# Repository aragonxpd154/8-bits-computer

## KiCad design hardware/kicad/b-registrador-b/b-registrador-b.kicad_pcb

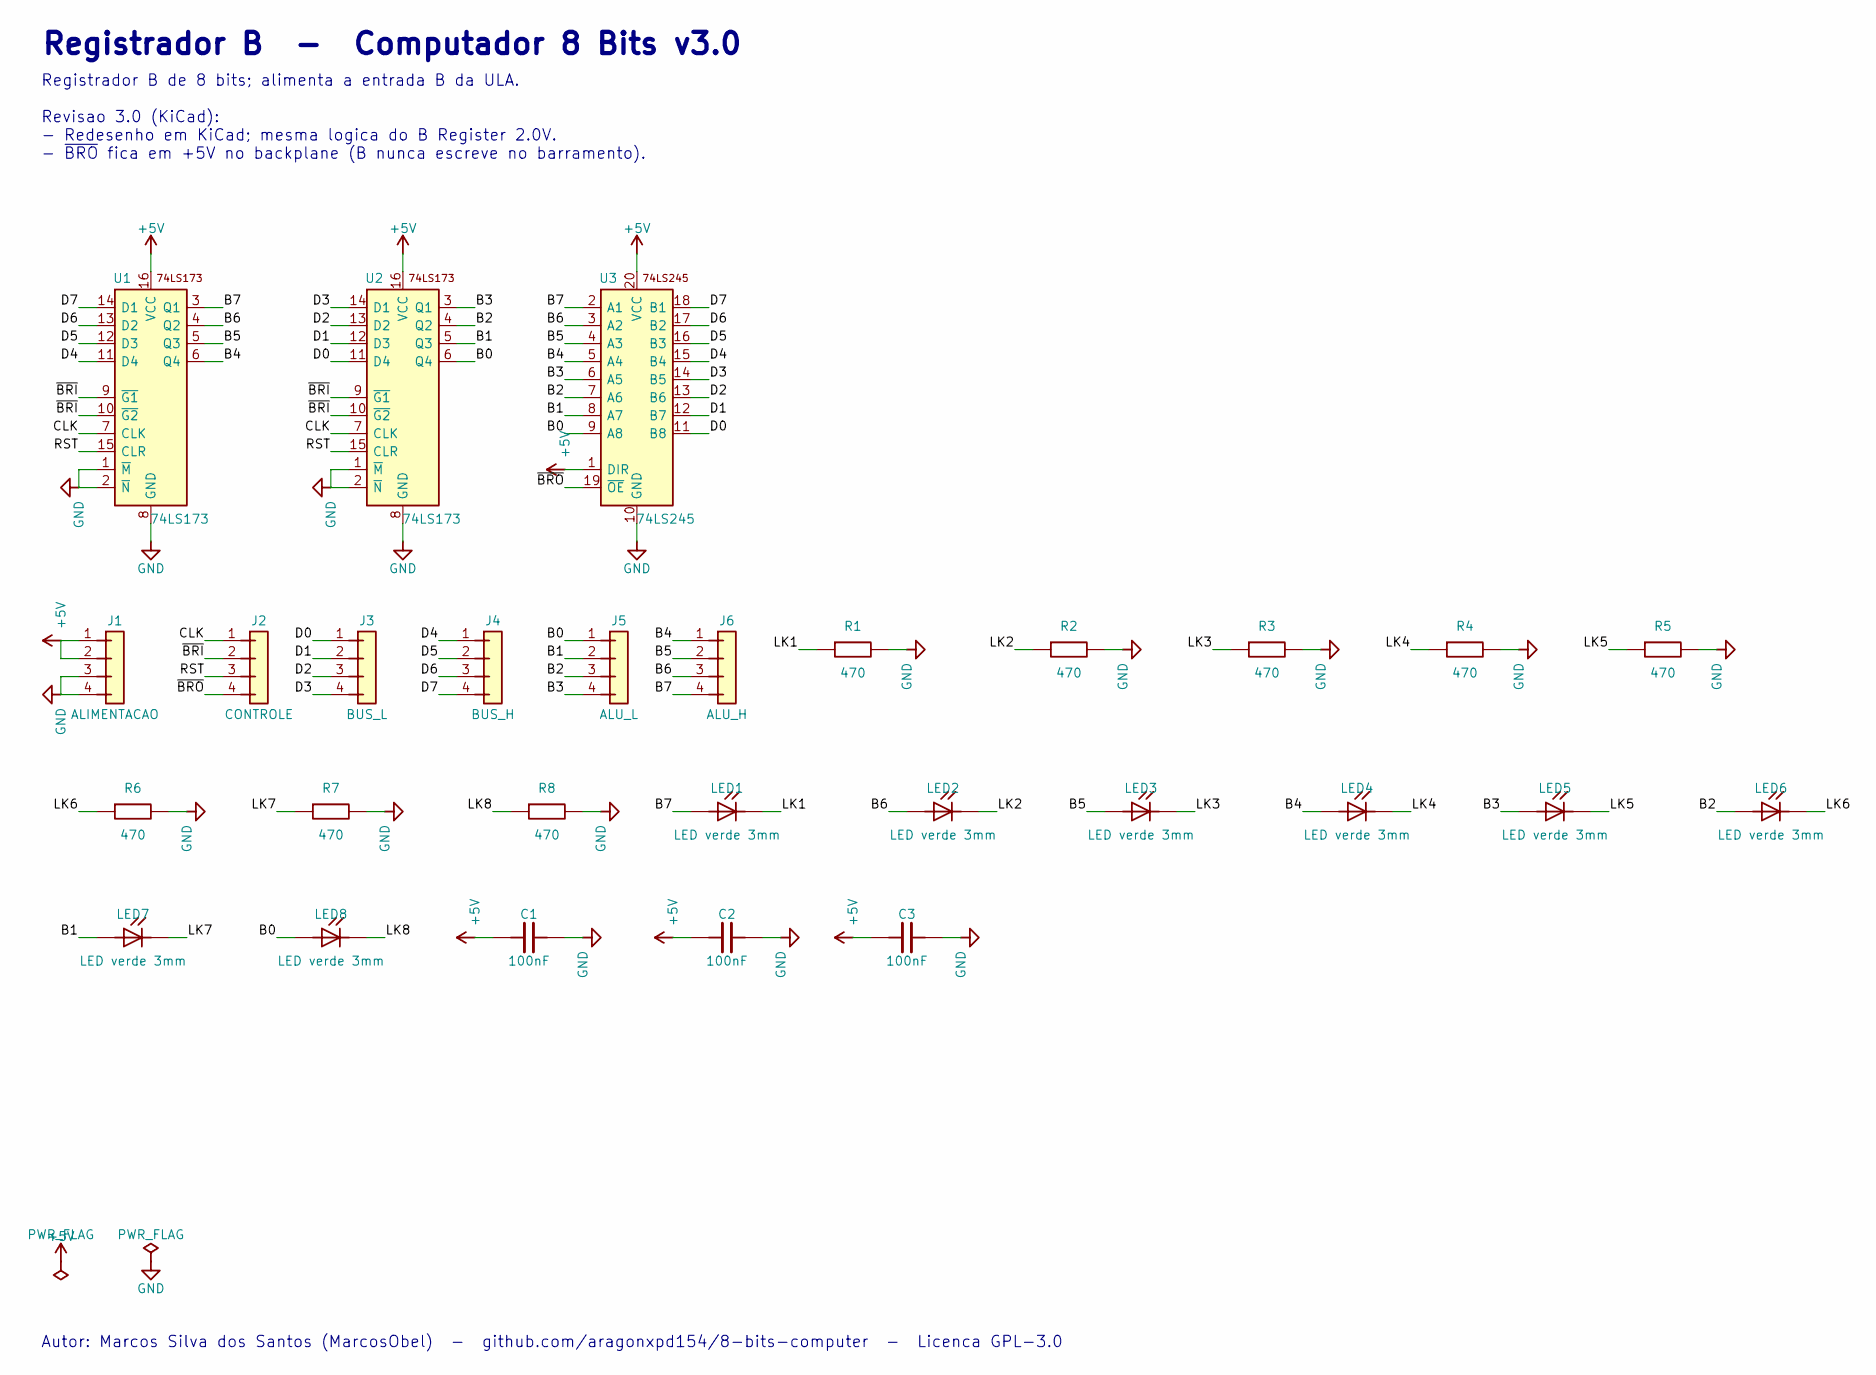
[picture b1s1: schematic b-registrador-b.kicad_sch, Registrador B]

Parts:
C1, C2, C3: 100nF; C_Disc_D5.0mm_W2.5mm_P5.00mm
J1: ALIMENTACAO; PinHeader_1x04_P2.54mm_Vertical
J2: CONTROLE; PinHeader_1x04_P2.54mm_Vertical
J3: BUS_L; PinHeader_1x04_P2.54mm_Vertical
J4: BUS_H; PinHeader_1x04_P2.54mm_Vertical
J5: ALU_L; PinHeader_1x04_P2.54mm_Vertical
J6: ALU_H; PinHeader_1x04_P2.54mm_Vertical
LED1, LED2, LED3, LED4, LED5, LED6, LED7, LED8: LED verde 3mm; LED_D3.0mm
R1, R2, R3, R4, R5, R6, R7, R8: 470; R_Axial_DIN0207_L6.3mm_D2.5mm_P10.16mm_Horizontal
U1, U2: 74LS173; DIP-16_W7.62mm_LongPads
U3: 74LS245; DIP-20_W7.62mm_LongPads

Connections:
+5V: C1.1, C2.1, C3.1, J1.1, J1.2, U1.16 (VCC), U2.16 (VCC), U3.1 (DIR), U3.20 (VCC)
B0: J5.1, LED8.2 (A), U2.6 (Q4), U3.9 (A8)
B1: J5.2, LED7.2 (A), U2.5 (Q3), U3.8 (A7)
B2: J5.3, LED6.2 (A), U2.4 (Q2), U3.7 (A6)
B3: J5.4, LED5.2 (A), U2.3 (Q1), U3.6 (A5)
B4: J6.1, LED4.2 (A), U1.6 (Q4), U3.5 (A4)
B5: J6.2, LED3.2 (A), U1.5 (Q3), U3.4 (A3)
B6: J6.3, LED2.2 (A), U1.4 (Q2), U3.3 (A2)
B7: J6.4, LED1.2 (A), U1.3 (Q1), U3.2 (A1)
CLK: J2.1, U1.7 (CLK), U2.7 (CLK)
D0: J3.1, U2.11 (D4), U3.11 (B8)
D1: J3.2, U2.12 (D3), U3.12 (B7)
D2: J3.3, U2.13 (D2), U3.13 (B6)
D3: J3.4, U2.14 (D1), U3.14 (B5)
D4: J4.1, U1.11 (D4), U3.15 (B4)
D5: J4.2, U1.12 (D3), U3.16 (B3)
D6: J4.3, U1.13 (D2), U3.17 (B2)
D7: J4.4, U1.14 (D1), U3.18 (B1)
GND: C1.2, C2.2, C3.2, J1.3, J1.4, R1.2, R2.2, R3.2, R4.2, R5.2, R6.2, R7.2, R8.2, U1.1 (~M), U1.2 (~N), U1.8 (GND), U2.1 (~M), U2.2 (~N), U2.8 (GND), U3.10 (GND)
LK1: LED1.1 (K), R1.1
LK2: LED2.1 (K), R2.1
LK3: LED3.1 (K), R3.1
LK4: LED4.1 (K), R4.1
LK5: LED5.1 (K), R5.1
LK6: LED6.1 (K), R6.1
LK7: LED7.1 (K), R7.1
LK8: LED8.1 (K), R8.1
RST: J2.3, U1.15 (CLR), U2.15 (CLR)
~BRI: J2.2, U1.9 (~G1), U1.10 (~G2), U2.9 (~G1), U2.10 (~G2)
~BRO: J2.4, U3.19 (~OE)

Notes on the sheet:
Registrador B - Computador 8 Bits v3.0
Registrador B de 8 bits; alimenta a entrada B da ULA. Revisao 3.0 (KiCad): - Redesenho em KiCad; mesma logica do B Register 2.0V. - ~{BRO} fica em +5V no backplane (B nunca escreve no barramento).
Autor: Marcos Silva dos Santos (MarcosObel) - github.com/aragonxpd154/8-bits-computer - Licenca GPL-3.0

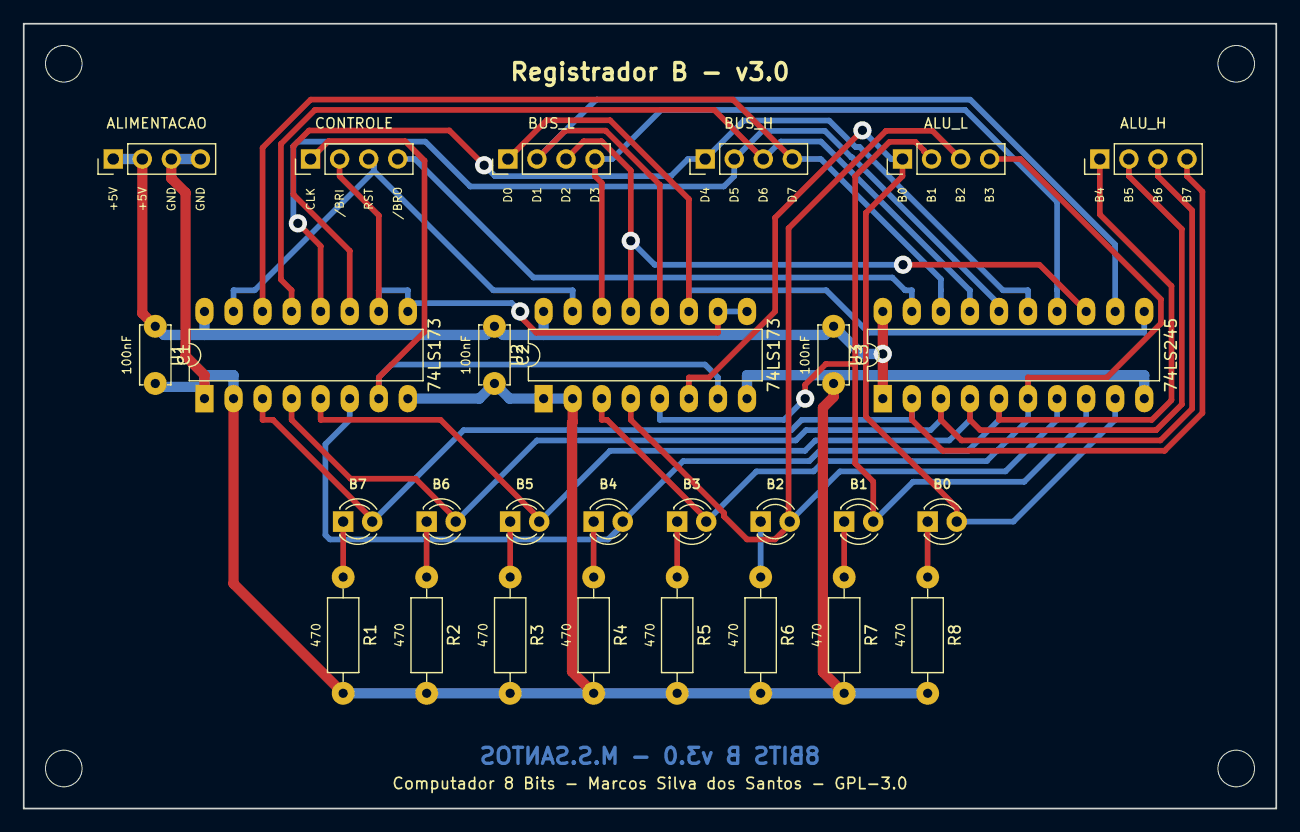
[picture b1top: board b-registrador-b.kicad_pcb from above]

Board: 2 copper layers, 109.5 x 68.6 mm, 32 parts (0 on the bottom side), 30 nets.

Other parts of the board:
H1, H2, H3, H4: MountingHole_3.2mm_M3

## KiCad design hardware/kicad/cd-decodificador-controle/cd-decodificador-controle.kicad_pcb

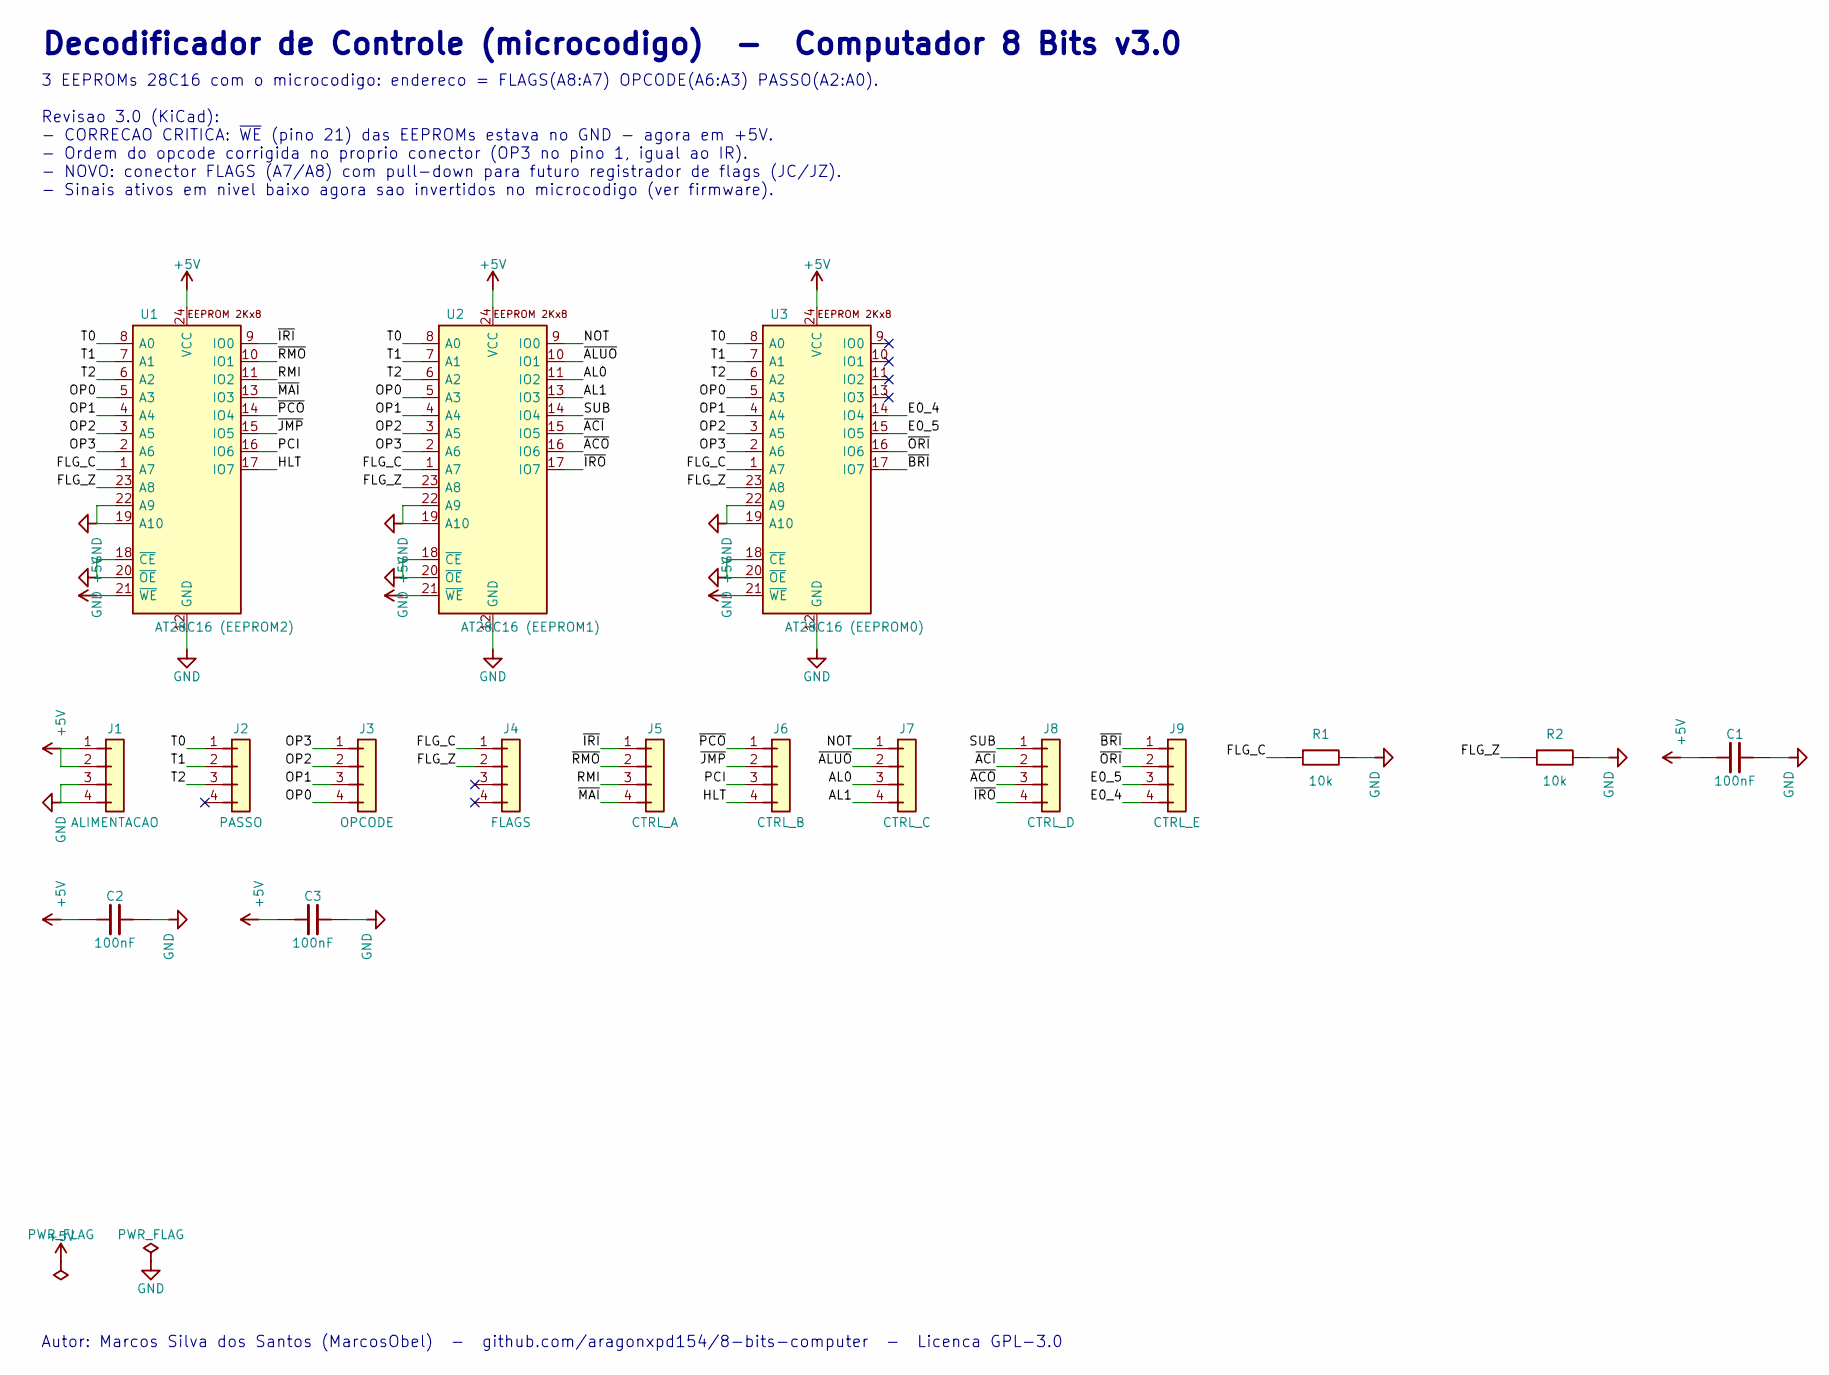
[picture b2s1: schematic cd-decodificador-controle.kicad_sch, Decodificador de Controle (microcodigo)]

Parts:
C1, C2, C3: 100nF; C_Disc_D5.0mm_W2.5mm_P5.00mm
J1: ALIMENTACAO; PinHeader_1x04_P2.54mm_Vertical
J2: PASSO; PinHeader_1x04_P2.54mm_Vertical
J3: OPCODE; PinHeader_1x04_P2.54mm_Vertical
J4: FLAGS; PinHeader_1x04_P2.54mm_Vertical
J5: CTRL_A; PinHeader_1x04_P2.54mm_Vertical
J6: CTRL_B; PinHeader_1x04_P2.54mm_Vertical
J7: CTRL_C; PinHeader_1x04_P2.54mm_Vertical
J8: CTRL_D; PinHeader_1x04_P2.54mm_Vertical
J9: CTRL_E; PinHeader_1x04_P2.54mm_Vertical
R1, R2: 10k; R_Axial_DIN0207_L6.3mm_D2.5mm_P10.16mm_Horizontal
U1: AT28C16 (EEPROM2); DIP-24_W15.24mm_LongPads
U2: AT28C16 (EEPROM1); DIP-24_W15.24mm_LongPads
U3: AT28C16 (EEPROM0); DIP-24_W15.24mm_LongPads

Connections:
+5V: C1.1, C2.1, C3.1, J1.1, J1.2, U1.21 (~WE), U1.24 (VCC), U2.21 (~WE), U2.24 (VCC), U3.21 (~WE), U3.24 (VCC)
AL0: J7.3, U2.11 (IO2)
AL1: J7.4, U2.13 (IO3)
E0_4: J9.4, U3.14 (IO4)
E0_5: J9.3, U3.15 (IO5)
FLG_C: J4.1, R1.1, U1.1 (A7), U2.1 (A7), U3.1 (A7)
FLG_Z: J4.2, R2.1, U1.23 (A8), U2.23 (A8), U3.23 (A8)
GND: C1.2, C2.2, C3.2, J1.3, J1.4, R1.2, R2.2, U1.12 (GND), U1.18 (~CE), U1.19 (A10), U1.20 (~OE), U1.22 (A9), U2.12 (GND), U2.18 (~CE), U2.19 (A10), U2.20 (~OE), U2.22 (A9), U3.12 (GND), U3.18 (~CE), U3.19 (A10), U3.20 (~OE), U3.22 (A9)
HLT: J6.4, U1.17 (IO7)
NOT: J7.1, U2.9 (IO0)
OP0: J3.4, U1.5 (A3), U2.5 (A3), U3.5 (A3)
OP1: J3.3, U1.4 (A4), U2.4 (A4), U3.4 (A4)
OP2: J3.2, U1.3 (A5), U2.3 (A5), U3.3 (A5)
OP3: J3.1, U1.2 (A6), U2.2 (A6), U3.2 (A6)
PCI: J6.3, U1.16 (IO6)
RMI: J5.3, U1.11 (IO2)
SUB: J8.1, U2.14 (IO4)
T0: J2.1, U1.8 (A0), U2.8 (A0), U3.8 (A0)
T1: J2.2, U1.7 (A1), U2.7 (A1), U3.7 (A1)
T2: J2.3, U1.6 (A2), U2.6 (A2), U3.6 (A2)
~ACI: J8.2, U2.15 (IO5)
~ACO: J8.3, U2.16 (IO6)
~ALUO: J7.2, U2.10 (IO1)
~BRI: J9.1, U3.17 (IO7)
~IRI: J5.1, U1.9 (IO0)
~IRO: J8.4, U2.17 (IO7)
~JMP: J6.2, U1.15 (IO5)
~MAI: J5.4, U1.13 (IO3)
~ORI: J9.2, U3.16 (IO6)
~PCO: J6.1, U1.14 (IO4)
~RMO: J5.2, U1.10 (IO1)

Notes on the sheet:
Decodificador de Controle (microcodigo) - Computador 8 Bits v3.0
3 EEPROMs 28C16 com o microcodigo: endereco = FLAGS(A8:A7) OPCODE(A6:A3) PASSO(A2:A0). Revisao 3.0 (KiCad): - CORRECAO CRITICA: ~{WE} (pino 21) das EEPROMs estava no GND - agora em +5V. - Ordem do opcode corrigida no proprio conector (OP3 no pino 1, igual ao IR). - NOVO: conector FLAGS (A7/A8) com 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
Autor: Marcos Silva dos Santos (MarcosObel) - github.com/aragonxpd154/8-bits-computer - Licenca GPL-3.0

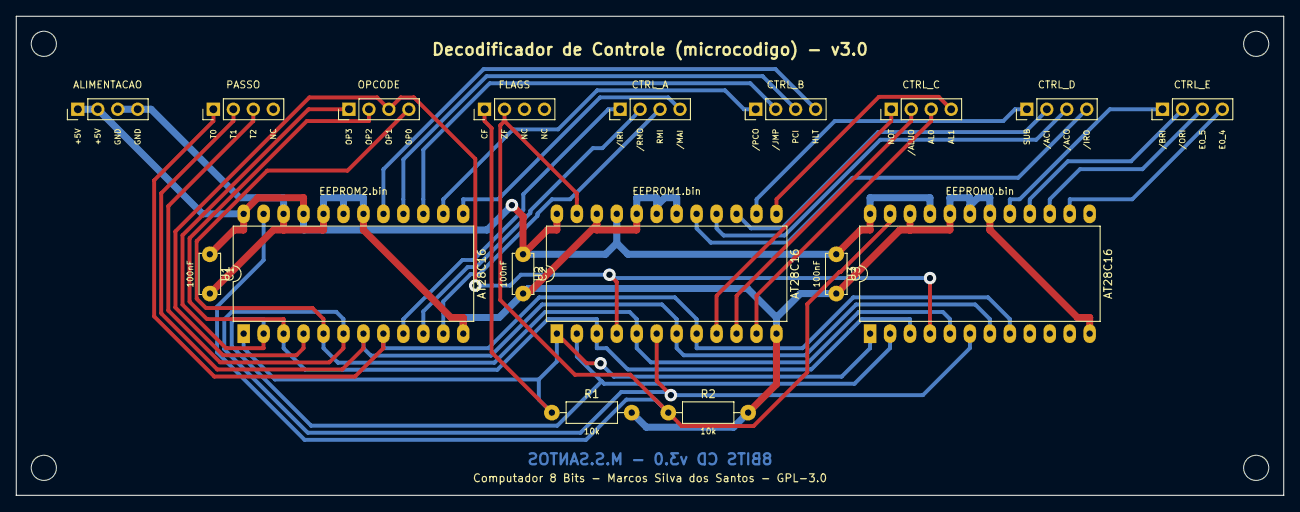
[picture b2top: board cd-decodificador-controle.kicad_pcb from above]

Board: 2 copper layers, 161.2 x 61.0 mm, 21 parts (0 on the bottom side), 31 nets.

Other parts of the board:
H1, H2, H3, H4: MountingHole_3.2mm_M3

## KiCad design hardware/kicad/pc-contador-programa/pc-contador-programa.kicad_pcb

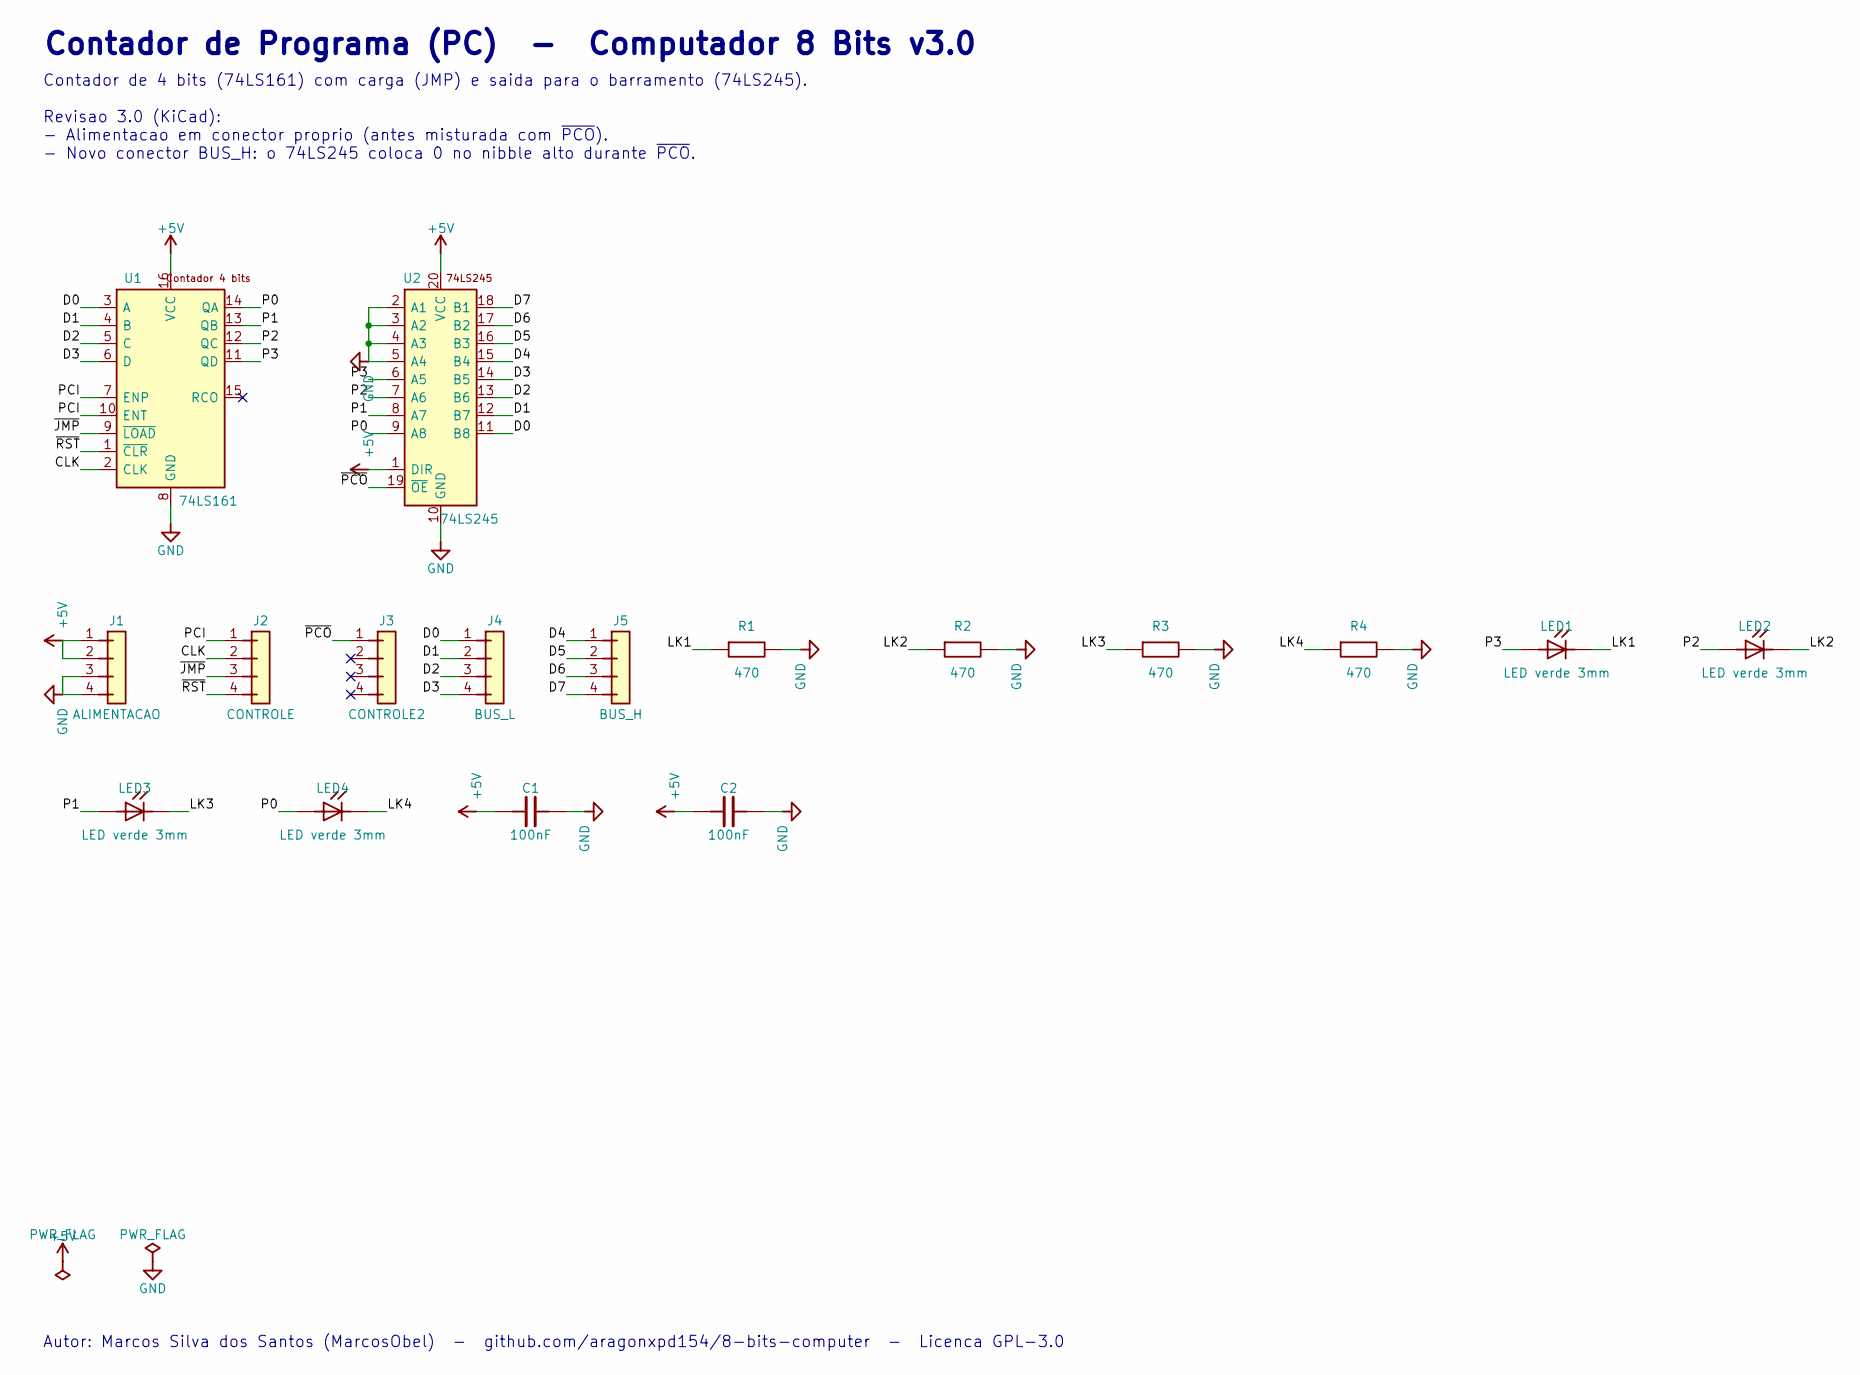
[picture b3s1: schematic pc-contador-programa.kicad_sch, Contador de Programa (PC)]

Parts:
C1, C2: 100nF; C_Disc_D5.0mm_W2.5mm_P5.00mm
J1: ALIMENTACAO; PinHeader_1x04_P2.54mm_Vertical
J2: CONTROLE; PinHeader_1x04_P2.54mm_Vertical
J3: CONTROLE2; PinHeader_1x04_P2.54mm_Vertical
J4: BUS_L; PinHeader_1x04_P2.54mm_Vertical
J5: BUS_H; PinHeader_1x04_P2.54mm_Vertical
LED1, LED2, LED3, LED4: LED verde 3mm; LED_D3.0mm
R1, R2, R3, R4: 470; R_Axial_DIN0207_L6.3mm_D2.5mm_P10.16mm_Horizontal
U1: 74LS161; DIP-16_W7.62mm_LongPads
U2: 74LS245; DIP-20_W7.62mm_LongPads

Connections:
+5V: C1.1, C2.1, J1.1, J1.2, U1.16 (VCC), U2.1 (DIR), U2.20 (VCC)
CLK: J2.2, U1.2 (CLK)
D0: J4.1, U1.3 (A), U2.11 (B8)
D1: J4.2, U1.4 (B), U2.12 (B7)
D2: J4.3, U1.5 (C), U2.13 (B6)
D3: J4.4, U1.6 (D), U2.14 (B5)
D4: J5.1, U2.15 (B4)
D5: J5.2, U2.16 (B3)
D6: J5.3, U2.17 (B2)
D7: J5.4, U2.18 (B1)
GND: C1.2, C2.2, J1.3, J1.4, R1.2, R2.2, R3.2, R4.2, U1.8 (GND), U2.2 (A1), U2.3 (A2), U2.4 (A3), U2.5 (A4), U2.10 (GND)
LK1: LED1.1 (K), R1.1
LK2: LED2.1 (K), R2.1
LK3: LED3.1 (K), R3.1
LK4: LED4.1 (K), R4.1
P0: LED4.2 (A), U1.14 (QA), U2.9 (A8)
P1: LED3.2 (A), U1.13 (QB), U2.8 (A7)
P2: LED2.2 (A), U1.12 (QC), U2.7 (A6)
P3: LED1.2 (A), U1.11 (QD), U2.6 (A5)
PCI: J2.1, U1.7 (ENP), U1.10 (ENT)
~JMP: J2.3, U1.9 (~LOAD)
~PCO: J3.1, U2.19 (~OE)
~RST: J2.4, U1.1 (~CLR)

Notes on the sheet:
Contador de Programa (PC) - Computador 8 Bits v3.0
Contador de 4 bits (74LS161) com carga (JMP) e saida para o barramento (74LS245). Revisao 3.0 (KiCad): - Alimentacao em conector proprio (antes misturada com ~{PCO}). - Novo conector BUS_H: o 74LS245 coloca 0 no nibble alto durante ~{PCO}.
Autor: Marcos Silva dos Santos (MarcosObel) - github.com/aragonxpd154/8-bits-computer - Licenca GPL-3.0

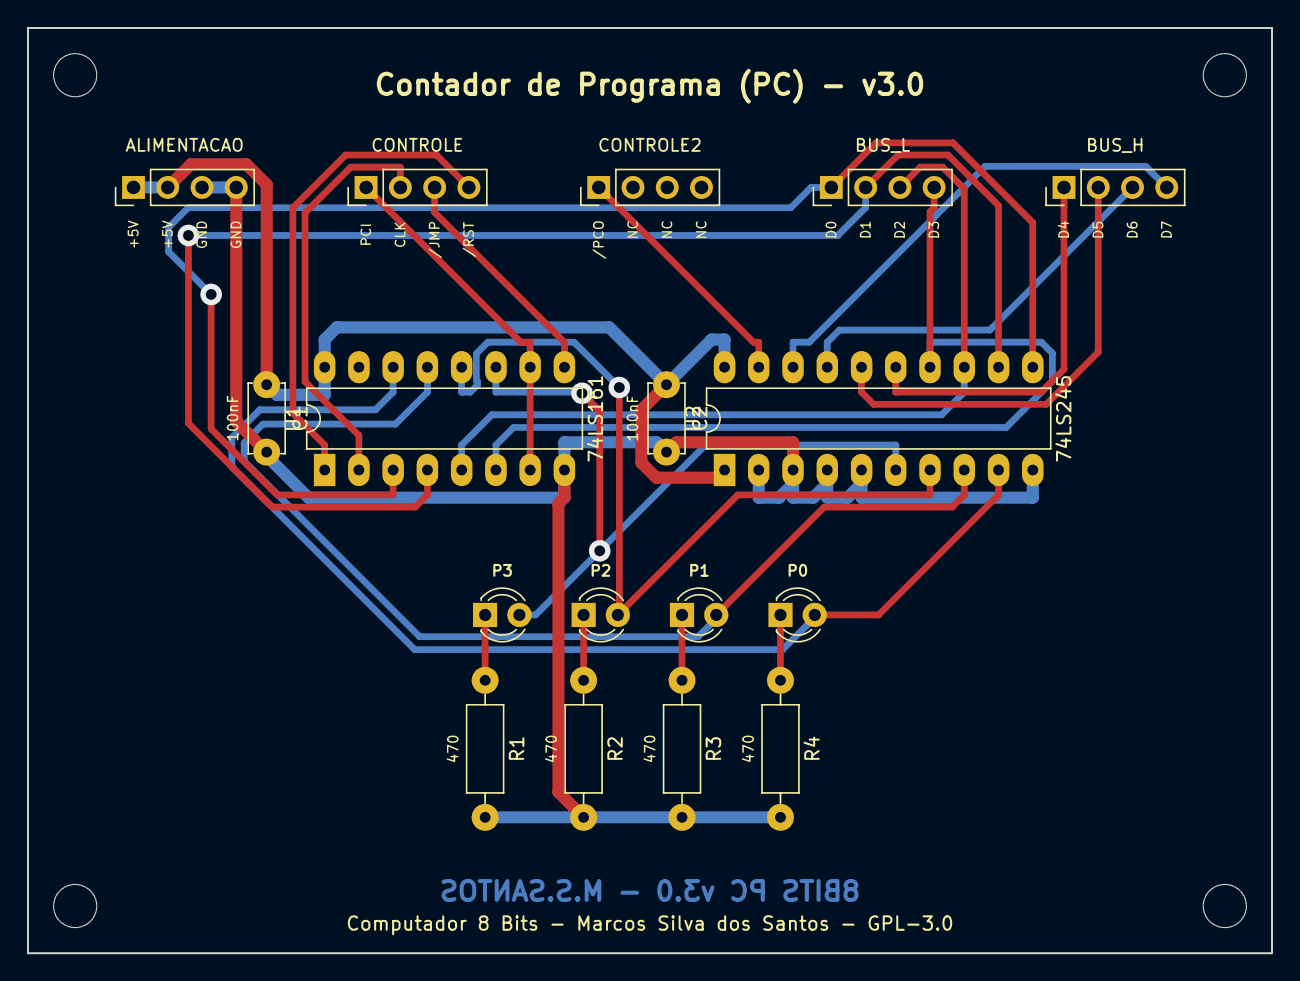
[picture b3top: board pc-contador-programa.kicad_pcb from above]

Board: 2 copper layers, 92.2 x 68.6 mm, 21 parts (0 on the bottom side), 23 nets.

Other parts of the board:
H1, H2, H3, H4: MountingHole_3.2mm_M3

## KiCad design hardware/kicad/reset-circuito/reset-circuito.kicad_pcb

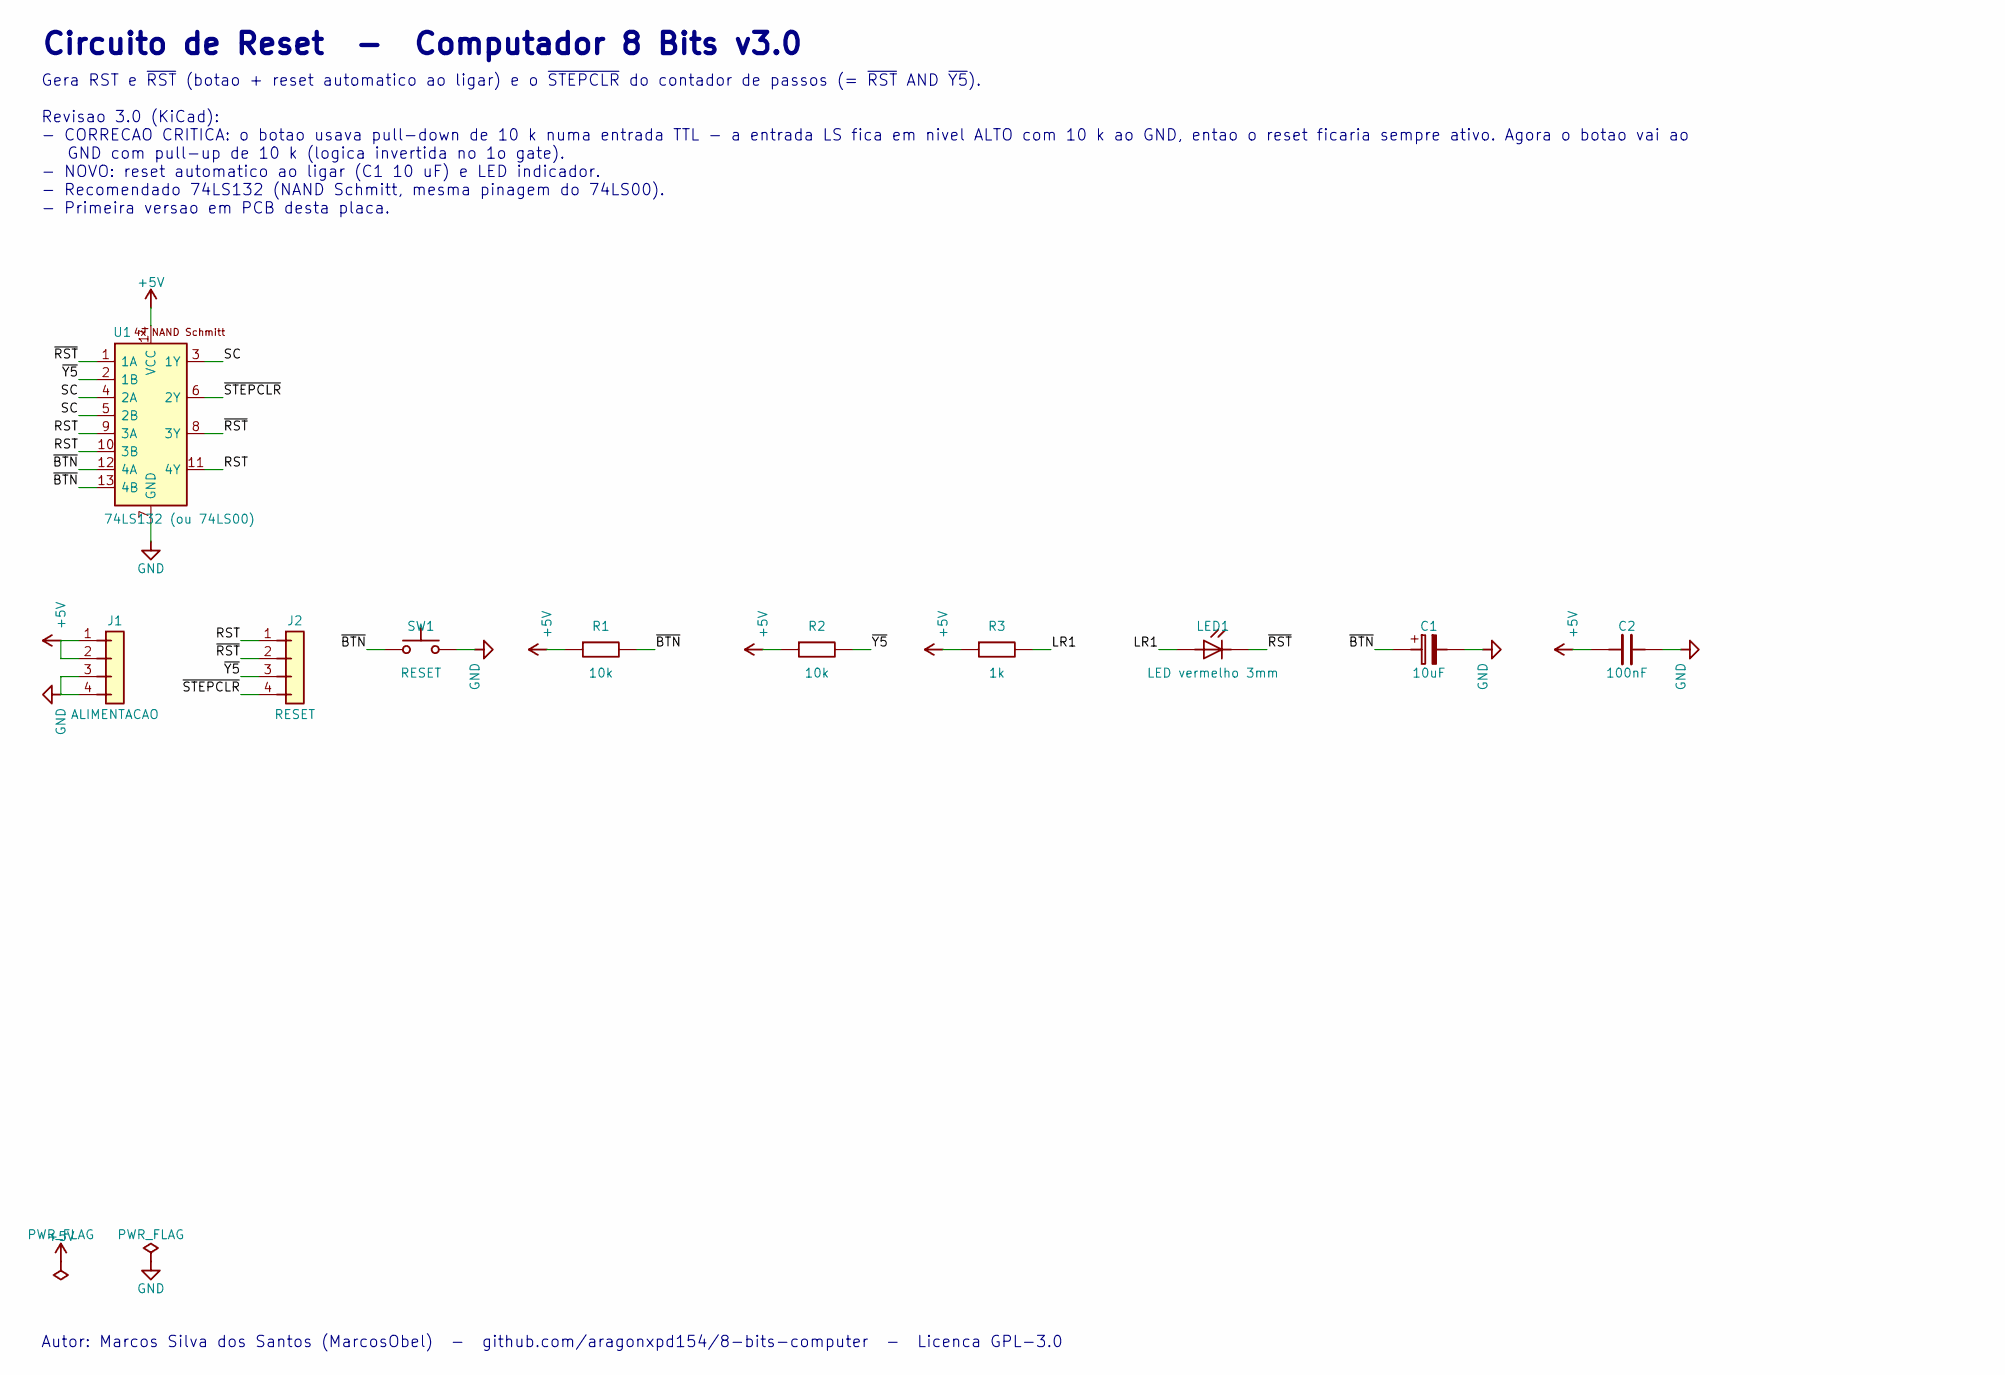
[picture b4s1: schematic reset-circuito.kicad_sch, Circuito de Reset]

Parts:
C1: 10uF; CP_Radial_D5.0mm_P2.00mm
C2: 100nF; C_Disc_D5.0mm_W2.5mm_P5.00mm
J1: ALIMENTACAO; PinHeader_1x04_P2.54mm_Vertical
J2: RESET; PinHeader_1x04_P2.54mm_Vertical
LED1: LED vermelho 3mm; LED_D3.0mm
R1, R2: 10k; R_Axial_DIN0207_L6.3mm_D2.5mm_P10.16mm_Horizontal
R3: 1k; R_Axial_DIN0207_L6.3mm_D2.5mm_P10.16mm_Horizontal
SW1: RESET; SW_PUSH_6mm
U1: 74LS132 (ou 74LS00); DIP-14_W7.62mm_LongPads

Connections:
+5V: C2.1, J1.1, J1.2, R1.1, R2.1, R3.1, U1.14 (VCC)
GND: C1.2, C2.2, J1.3, J1.4, SW1.2, U1.7 (GND)
LR1: LED1.2 (A), R3.2
RST: J2.1, U1.9 (3A), U1.10 (3B), U1.11 (4Y)
SC: U1.3 (1Y), U1.4 (2A), U1.5 (2B)
~BTN: C1.1, R1.2, SW1.1, U1.12 (4A), U1.13 (4B)
~RST: J2.2, LED1.1 (K), U1.1 (1A), U1.8 (3Y)
~STEPCLR: J2.4, U1.6 (2Y)
~Y5: J2.3, R2.2, U1.2 (1B)

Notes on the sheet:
Circuito de Reset - Computador 8 Bits v3.0
Gera RST e ~{RST} (botao + reset automatico ao ligar) e o ~{STEPCLR} do contador de passos (= ~{RST} AND ~{Y5}). Revisao 3.0 (KiCad): - CORRECAO CRITICA: o botao usava pull-down de 10 k numa entrada TTL - a entrada LS fica em nivel ALTO com 10 k ao GND, entao o reset ficaria sempre ativo. Agora o b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
Autor: Marcos Silva dos Santos (MarcosObel) - github.com/aragonxpd154/8-bits-computer - Licenca GPL-3.0

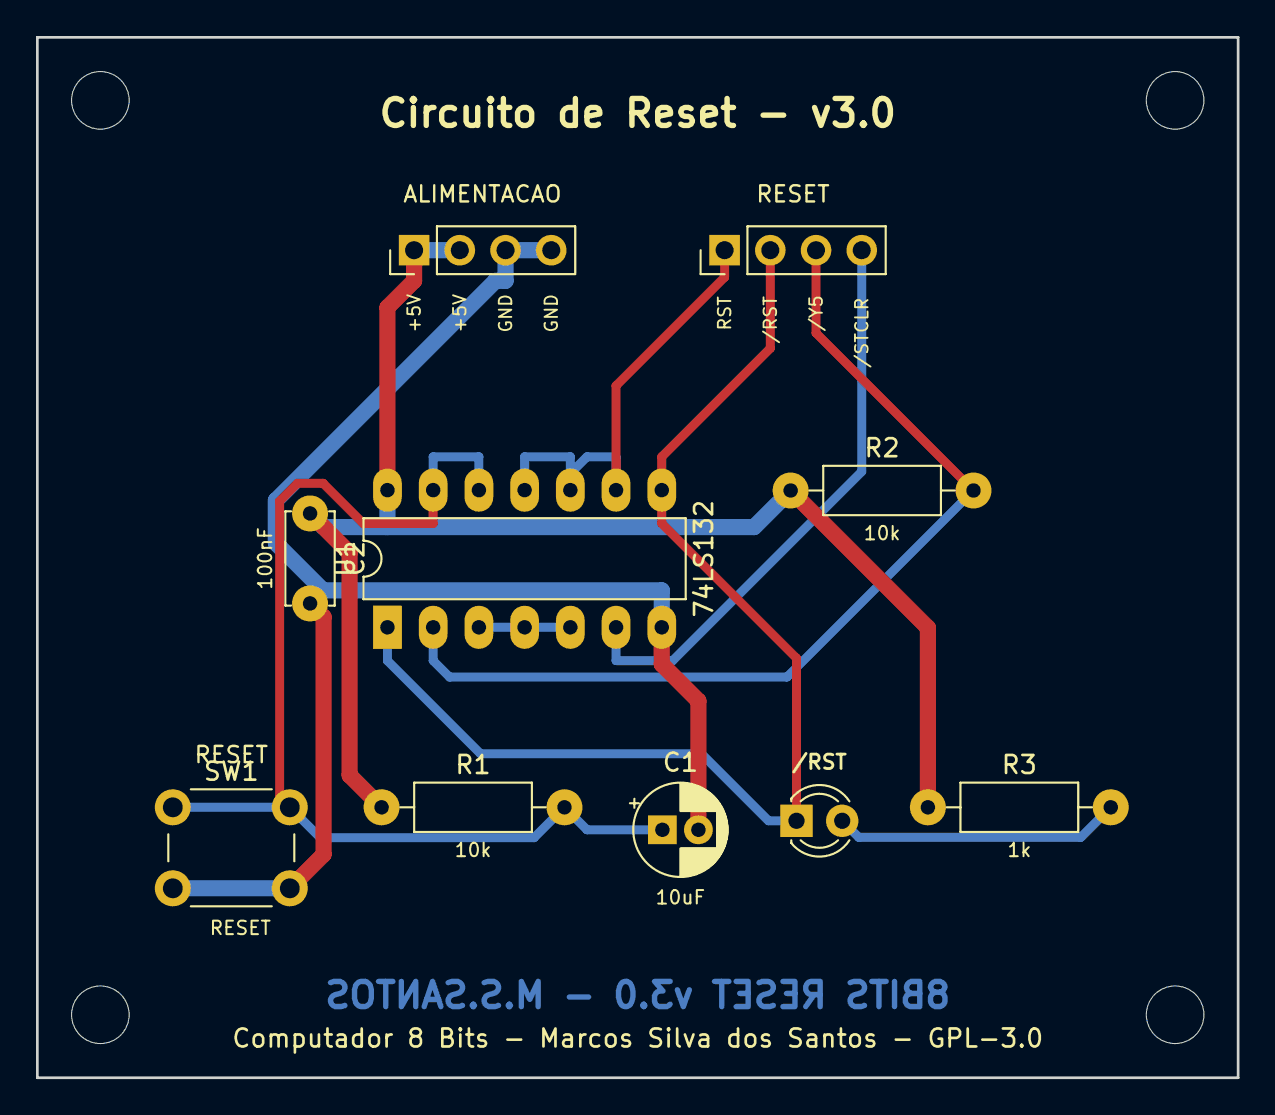
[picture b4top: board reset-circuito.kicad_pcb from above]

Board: 2 copper layers, 66.7 x 57.8 mm, 14 parts (0 on the bottom side), 9 nets.

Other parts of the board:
H1, H2, H3, H4: MountingHole_3.2mm_M3

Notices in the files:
hardware/kicad/b-registrador-b/b-registrador-b.kicad_pcb:
github.com/aragonxpd154/8-bits-computer - GPL-3.0
Computador 8 Bits - Marcos Silva dos Santos - GPL-3.0
hardware/kicad/b-registrador-b/b-registrador-b.kicad_sch:
Licenca GPL-3.0 - Computador 8 Bits sem microcontrolador
